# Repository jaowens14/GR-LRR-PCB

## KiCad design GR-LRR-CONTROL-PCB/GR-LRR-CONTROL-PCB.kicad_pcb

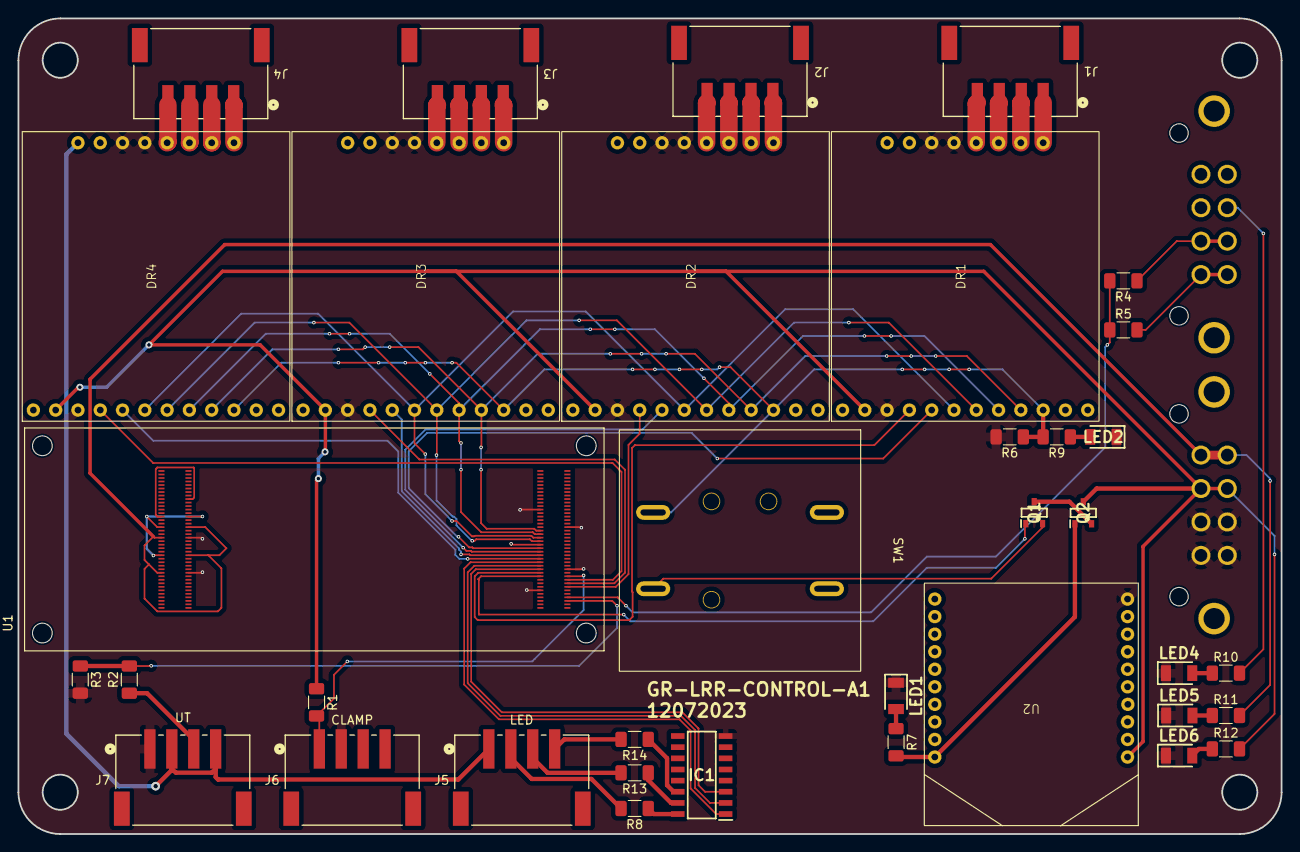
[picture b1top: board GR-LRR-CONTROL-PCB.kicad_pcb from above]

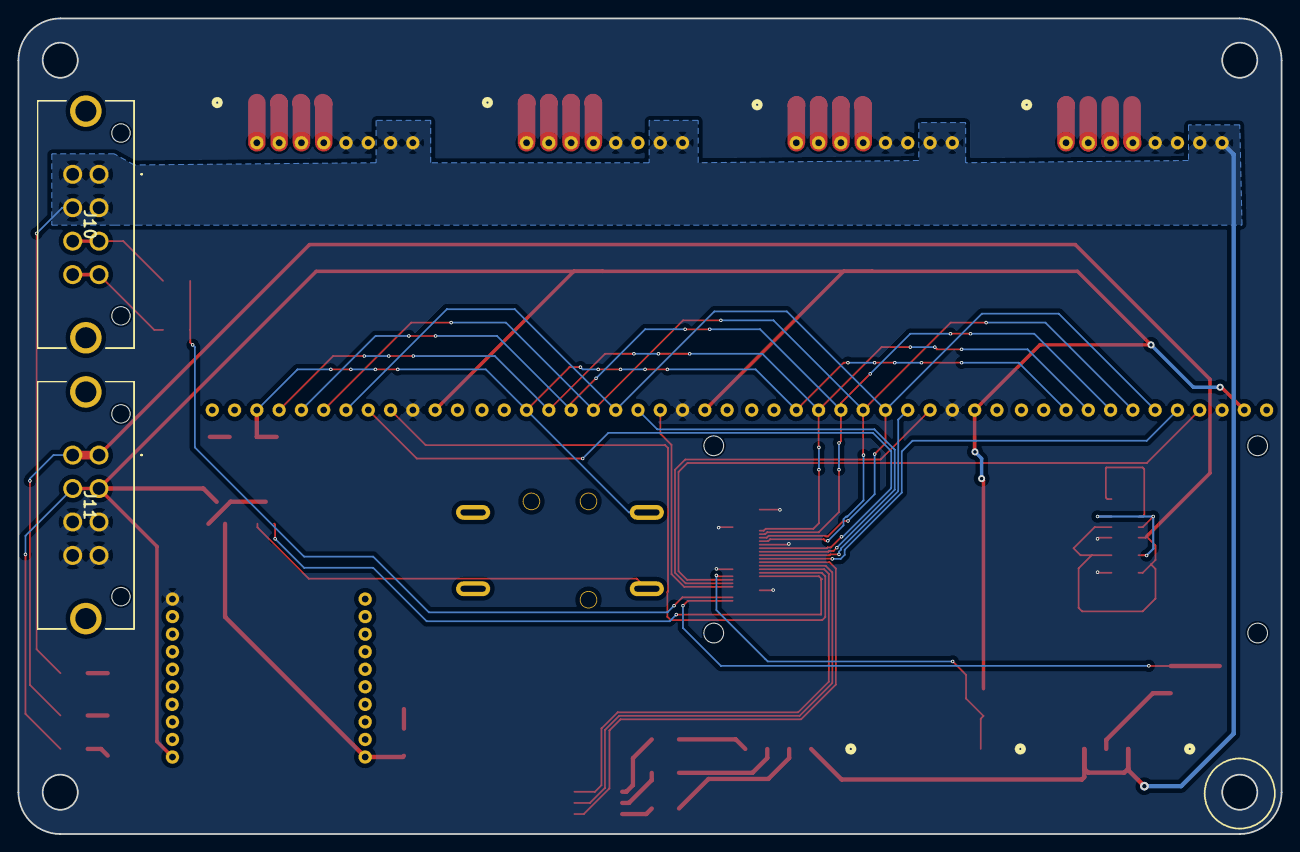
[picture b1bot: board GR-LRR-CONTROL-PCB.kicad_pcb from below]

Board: 2 copper layers, 143.9 x 92.9 mm, 38 parts (2 on the bottom side), 59 nets.

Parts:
DR1, DR2, DR3, DR4: 3730
IC1: MC1413DR2G; SOIC127P600X175-16N
J1: DRIVER 1; CONN_S4B-XH-SM4-TB_JST
J2: DRIVER 3; CONN_S4B-XH-SM4-TB_JST
J3: DRIVER 2; CONN_S4B-XH-SM4-TB_JST
J4: DRIVER 4; CONN_S4B-XH-SM4-TB_JST
J5: LED; CONN_S4B-XH-SM4-TB_JST
J6: CLAMP; CONN_S4B-XH-SM4-TB_JST
J7: UT; CONN_S4B-XH-SM4-TB_JST
J10, J11: FX30B-4S-3.81DSA; FX30B4S381DSA
LED1, LED2, LED4, LED5, LED6: QTLP650C2TR; LEDC3216X130N
Q1, Q2: BSS806NH6327XTSA1; SOT95P240X110-3N
R1, R4, R6, R8, R13, R14: 10k; R_1206_3216Metric_Pad1.30x1.75mm_HandSolder
R2: 4k; R_1206_3216Metric_Pad1.30x1.75mm_HandSolder
R3, R5: 1k; R_1206_3216Metric_Pad1.30x1.75mm_HandSolder
R7, R9, R12: 75ohm, 1/10w; R_1206_3216Metric_Pad1.30x1.75mm_HandSolder
R10: 1200ohm, 0.5w; R_1206_3216Metric_Pad1.30x1.75mm_HandSolder
R11: 180ohm, 1/10w; R_1206_3216Metric_Pad1.30x1.75mm_HandSolder
SW1: XA1E-BV302-R
U1: ABX00042; MODULE_ABX00042
U2: XB3-24AST-J

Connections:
73_ANALOG_A0: R4.2, R5.1, U1.J2_73 (ADC_A0)
75_ANALOG_A1: R2.2, R3.1, U1.J2_75 (ADC_A1)
+3.3V: DR1.2 (IOREF), DR2.2 (IOREF), DR3.2 (IOREF), DR4.2 (IOREF), J11.A2, J11.B2, Q2.3 (D), R1.1, R12.2, U2.1 (VCC)
+5V: J11.A1, J11.B1, R11.2, U1.J1_21 (VIN), U1.J1_41 (VIN)
+24V: DR1.19 (MOTOR_VIN), DR1.20 (MOTOR_VIN), DR2.19 (MOTOR_VIN), DR2.20 (MOTOR_VIN), DR3.19 (MOTOR_VIN), DR3.20 (MOTOR_VIN), DR4.19 (MOTOR_VIN), DR4.20 (MOTOR_VIN), J5.1, J7.2, J7.4, J10.A1, J10.A2, J10.B1, J10.B2, R10.2
BATT+: J10.A3, J10.B3, R4.1
BATT-: J10.A4, J10.B4, R5.2
D0 STEPPER ENABLE: Q1.1 (G), U1.J2_62 (PWM_7)
D1 STEP 1: DR1.4 (STEP/AIN1), U1.J2_60 (PWM_6)
D2 STEP 2: DR2.4 (STEP/AIN1), U1.J2_67 (PWM_5)
D3 STEP 3: DR3.4 (STEP/AIN1), U1.J2_65 (PWM_4)
D4 STEP 4: DR4.4 (STEP/AIN1), U1.J2_63 (PWM_3)
D5 CLAMP: J6.1, R1.2, U1.J2_61 (PWM_2)
D7 CS: DR1.9 (SCS), DR2.9 (SCS), DR3.9 (SCS), DR4.9 (SCS), U1.J2_36 (SPI1_CS)
D8 COPI: DR1.7 (SDATI), DR2.7 (SDATI), DR3.7 (SDATI), DR4.7 (SDATI), U1.J2_42 (SPI1_MOSI)
D9 CK: DR1.8 (SCLK), DR2.8 (SCLK), DR3.8 (SCLK), DR4.8 (SCLK), U1.J2_38 (SPI1_CK)
D10 CIPO: DR1.6 (SDATO), DR2.6 (SDATO), DR3.6 (SDATO), DR4.6 (SDATO), U1.J2_40 (SPI1_MISO)
GND: DR1.3 (GND), DR1.17 (MOTOR_GND), DR1.18 (MOTOR_GND), DR2.3 (GND), DR2.17 (MOTOR_GND), DR2.18 (MOTOR_GND), DR3.3 (GND), DR3.17 (MOTOR_GND), DR3.18 (MOTOR_GND), DR4.3 (GND), DR4.17 (MOTOR_GND), DR4.18 (MOTOR_GND), IC1.8 (GND), J6.2, J7.1, J11.A3, J11.A4, J11.B3, J11.B4, LED1.1 (K), LED2.1 (K), LED4.1 (K), LED5.1 (K), LED6.1 (K), R3.2, R6.2, U1.J1_22 (GND), U1.J1_42 (GND), U1.J2_24 (GND_1), U1.J2_33 (GND_1), U1.J2_44 (GND_1), U1.J2_57 (GND_1), U1.J2_70 (GND_1), U2.10 (GND)
GPIO0 DIR 1: DR1.5 (DIR/AIN2), U1.J2_46 (GPIO_0)
GPIO1 DIR 2: DR2.5 (DIR/AIN2), U1.J2_48 (GPIO_1)
GPIO2 DIR 3: DR3.5 (DIR/AIN2), U1.J2_50 (GPIO_2)
GPIO3 DIR 4: DR4.5 (DIR/AIN2), U1.J2_52 (GPIO_3)
GPIO4 RED LED: IC1.1 (IN_1), U1.J2_54 (GPIO_4)
GPIO5 YELLOW LED: IC1.2 (IN_2), U1.J2_56 (GPIO_5)
GPIO6 GREEN LED: IC1.3 (IN_3), U1.J2_58 (GPIO_6)
unnamed: DR1.16 (AOUT1), J1.4
unnamed: DR1.15 (AOUT2), J1.3
unnamed: DR1.14 (BOUT1), J1.2
unnamed: DR1.13 (BOUT2), J1.1
unnamed: DR2.16 (AOUT1), J2.4
unnamed: DR2.15 (AOUT2), J2.3
unnamed: DR2.14 (BOUT1), J2.2
unnamed: DR2.13 (BOUT2), J2.1
unnamed: DR3.16 (AOUT1), J3.4
unnamed: DR3.15 (AOUT2), J3.3
unnamed: DR3.14 (BOUT1), J3.2
unnamed: DR3.13 (BOUT2), J3.1
unnamed: DR4.16 (AOUT1), J4.4
unnamed: DR4.15 (AOUT2), J4.3
unnamed: DR4.14 (BOUT1), J4.2
unnamed: DR4.13 (BOUT2), J4.1
unnamed: IC1.14 (OUT_5), R14.1
unnamed: IC1.15 (OUT_6), R13.1
unnamed: IC1.16 (OUT_7), R8.1
unnamed: J5.2, R8.2
unnamed: J5.3, R13.2
unnamed: J5.4, R14.2
unnamed: J7.3, R2.1
unnamed: LED1.2 (A), R7.1
unnamed: LED2.2 (A), R9.1
unnamed: LED4.2 (A), R10.1
unnamed: LED5.2 (A), R11.1
unnamed: LED6.2 (A), R12.1
unnamed: Q1.3 (D), Q2.2 (S)
unnamed: Q1.2 (S), SW1.3
unnamed: U1.J1_31 (GND), U1.J1_47 (GND), U1.J1_54 (GND)
unnamed: U1.J1_53 (VSYS), U1.J1_64 (VSYS)
STEPPER_ENABLE: DR1.10 (!SLEEP), DR2.10 (!SLEEP), DR3.10 (!SLEEP), DR4.10 (!SLEEP), R6.1, R9.2, SW1.4
ZIGBEE_IO: Q2.1 (G), R7.2, U2.20 (AD0/DIO0)

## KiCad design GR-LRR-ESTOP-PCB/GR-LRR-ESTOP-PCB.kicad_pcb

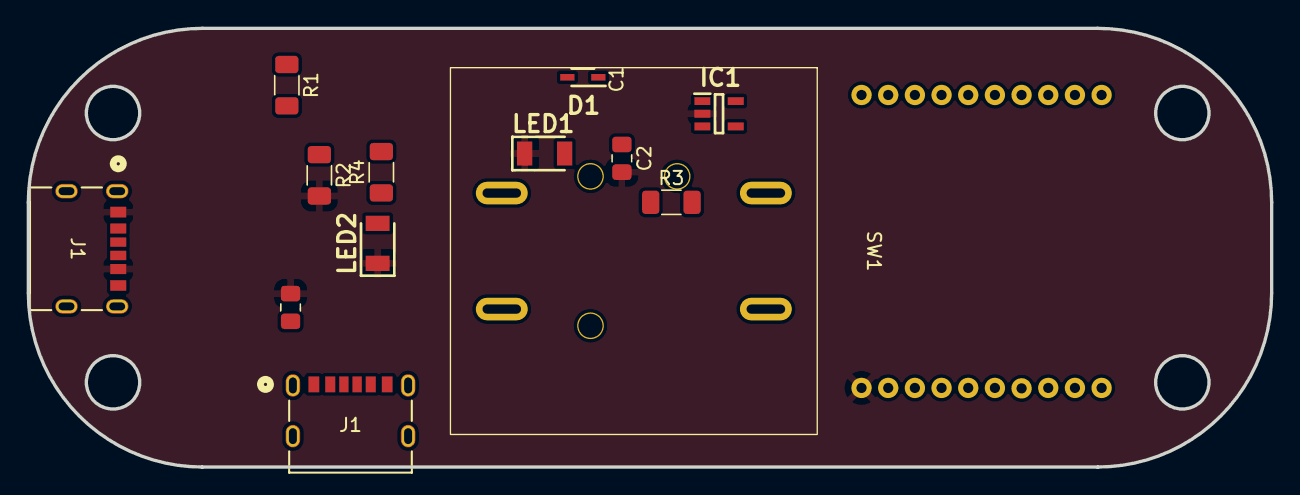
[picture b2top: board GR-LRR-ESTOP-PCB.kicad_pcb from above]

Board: 2 copper layers, 93.2 x 32.9 mm, 14 parts (1 on the bottom side), 8 nets, no tracks yet.

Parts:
C1, C2: 1uF, 10V; C_0805_2012Metric_Pad1.18x1.45mm_HandSolder
D1: ZLLS400TA; SOD2513X120N
IC1: TLV75533PDBVR; SOT95P280X145-5N
J1, J1#2: 10164359-00011LF; CONN_10164359-00011LF_AMP
LED1, LED2: QTLP650C2TR; LEDC3216X130N
R1, R2: 1k; R_1206_3216Metric_Pad1.30x1.75mm_HandSolder
R3, R4: 86ohm, 1/10w; R_1206_3216Metric_Pad1.30x1.75mm_HandSolder
SW1: XA1E-BV302-R
U1: XB3-24AST-J

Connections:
+3.3V: C2.1, IC1.5 (OUT), R3.2, SW1.1, U1.1 (VCC)
+5V: D1.2 (A), J1#2.A12 (VBUS), J1#2.B5 (VBUS)
GND: C1.2, C2.2, IC1.2 (GND), J1#2.A9 (GND), J1#2.B12 (GND), LED1.1 (K), LED2.1 (K), R2.2, U1.10 (GND)
unnamed: C1.1, D1.1 (K), IC1.1 (IN), IC1.3 (EN)
unnamed: LED1.2 (A), R3.1
unnamed: LED2.2 (A), R4.1
unnamed: R1.1, SW1.2
unnamed: R1.2, R2.1, R4.2, U1.20 (AD0/DIO0)

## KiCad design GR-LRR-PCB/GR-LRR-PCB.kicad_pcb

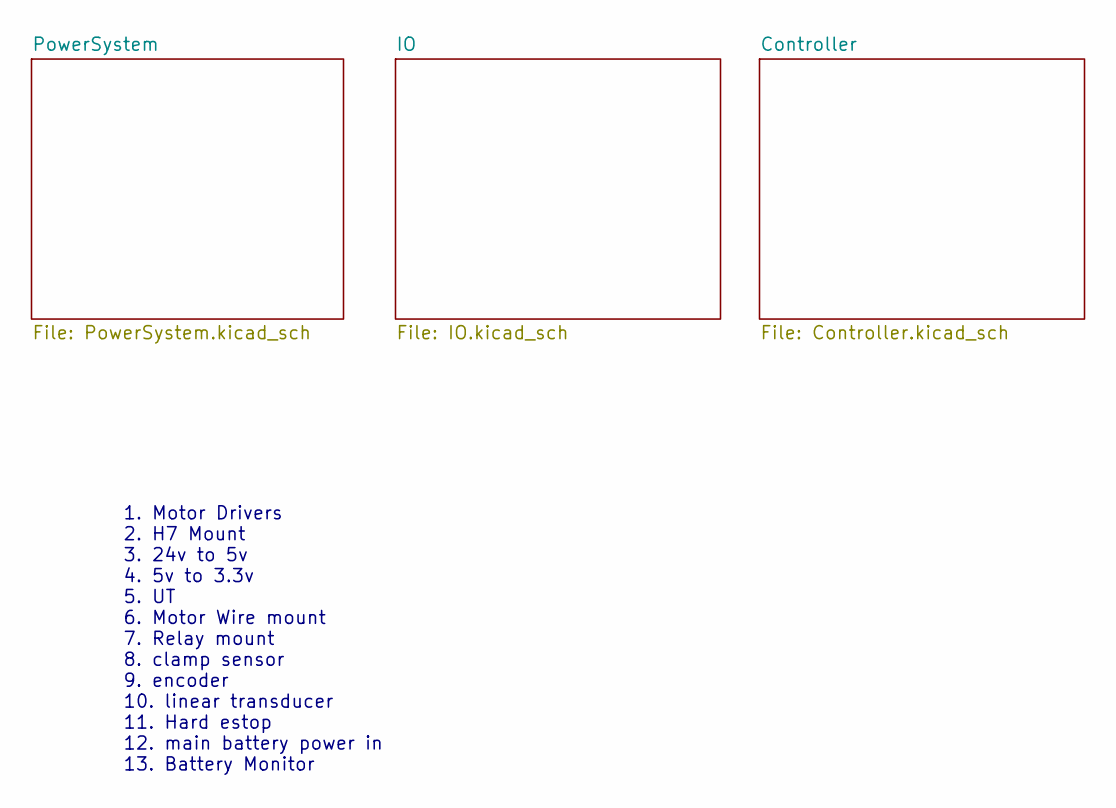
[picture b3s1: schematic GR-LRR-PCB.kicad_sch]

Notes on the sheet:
1. Motor Drivers 2. H7 Mount 3. 24v to 5v 4. 5v to 3.3v 5. UT 6. Motor Wire mount 7. Relay mount 8. clamp sensor 9. encoder 10. linear transducer 11. Hard estop 12. main battery power in 13. Battery Monitor

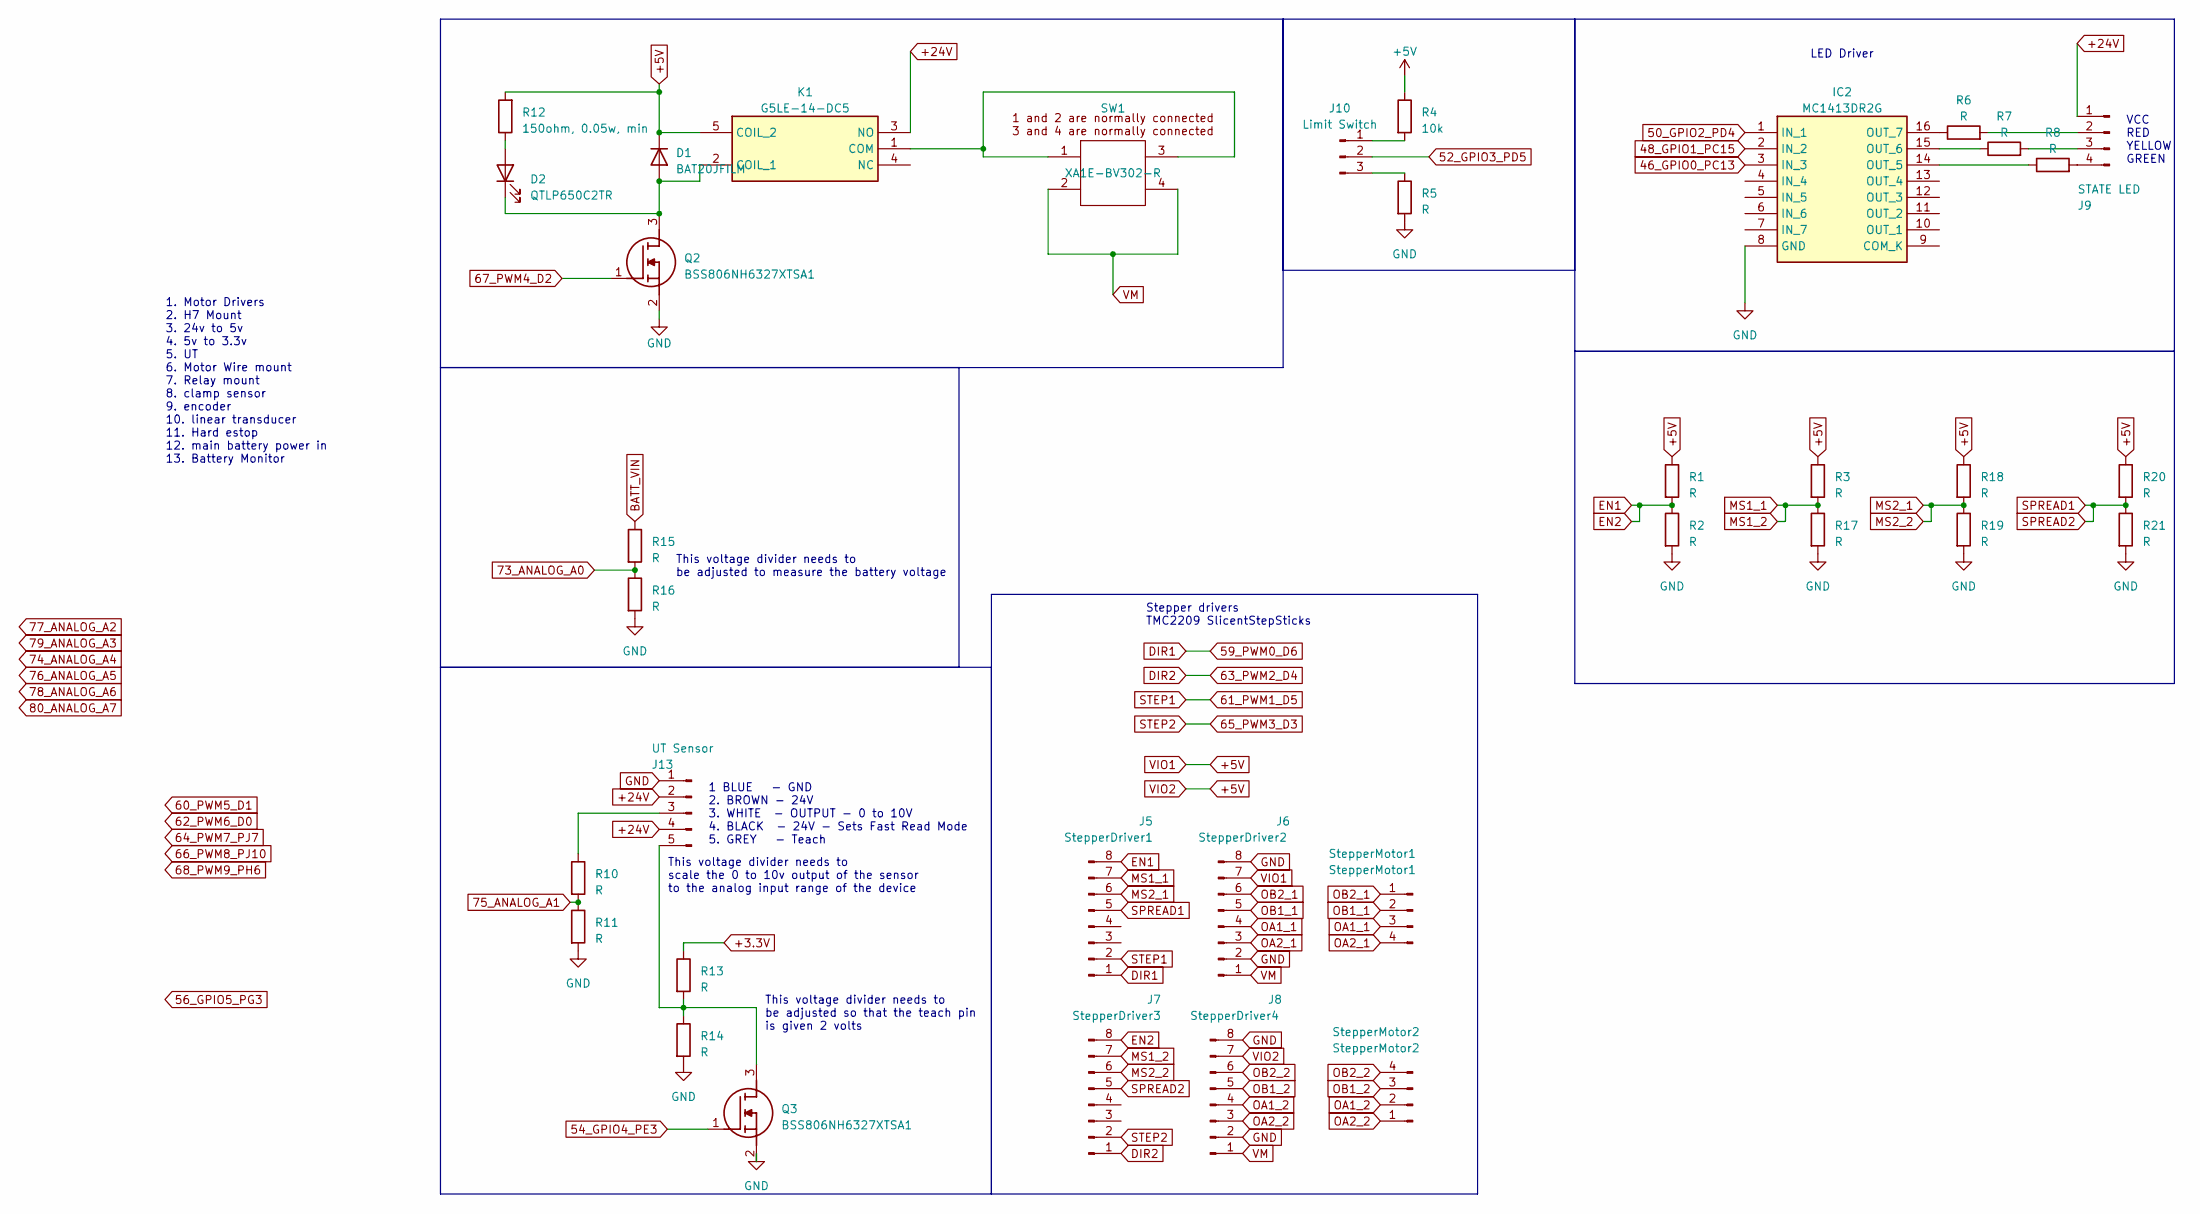
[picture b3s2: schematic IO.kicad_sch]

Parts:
D1: BAT20JFILM; D_SOD-323_HandSoldering
D2: QTLP650C2TR; D_1206_3216Metric_Pad1.42x1.75mm_HandSolder
IC2: MC1413DR2G; SOIC127P600X175-16N; Mouser Part Number 863-MC1413DR2G
J5: StepperDriver1; PinHeader_1x08_P2.54mm_Vertical
J6: StepperDriver2; PinHeader_1x08_P2.54mm_Vertical
J7: StepperDriver3; PinHeader_1x08_P2.54mm_Vertical
J8: StepperDriver4; PinHeader_1x08_P2.54mm_Vertical
J9: STATE LED; PinHeader_1x04_P2.54mm_Vertical; Part Number JR28-RYG-D
J10: Limit Switch; PinHeader_1x03_P2.54mm_Vertical
J13: UT Sensor; PinHeader_1x05_P2.54mm_Vertical
K1: G5LE-14-DC5; G5LE-14_SPDT; Mouser Part Number 653-G5LE-14-DC5
Q2, Q3: BSS806NH6327XTSA1; SOT95P240X110-3N; Mouser Part Number 726-BSS806NH6327
R1, R2, R3, R5, R6, R7, R8, R10, R11, R13, R14, R15, R16, R17, R18, R19, R20, R21: R; R_1206_3216Metric_Pad1.30x1.75mm_HandSolder
R4: 10k; R_1206_3216Metric_Pad1.30x1.75mm_HandSolder
R12: 150ohm, 0.05w, min; R_1206_3216Metric_Pad1.30x1.75mm_HandSolder; Part Number RMCF1206JT300R
SW1: XA1E-BV302-R
StepperMotor1: StepperMotor1; PinHeader_1x04_P2.54mm_Vertical
StepperMotor2: StepperMotor2; PinHeader_1x04_P2.54mm_Vertical

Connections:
46_GPIO0_PC13: IC2.3 (IN_3); also elsewhere on the board
48_GPIO1_PC15: IC2.2 (IN_2); also elsewhere on the board
50_GPIO2_PD4: IC2.1 (IN_1); also elsewhere on the board
52_GPIO3_PD5: J10.2; also elsewhere on the board
54_GPIO4_PE3: Q3.1 (G); also elsewhere on the board
59_PWM0_D6: J5.1; also elsewhere on the board
61_PWM1_D5: J5.2; also elsewhere on the board
63_PWM2_D4: J7.1; also elsewhere on the board
65_PWM3_D3: J7.2; also elsewhere on the board
67_PWM4_D2: Q2.1 (G); also elsewhere on the board
73_ANALOG_A0: R15.2, R16.1; also elsewhere on the board
75_ANALOG_A1: R10.2, R11.1; also elsewhere on the board
+3.3V: R13.1; also elsewhere on the board
+5V: D1.1 (K), J6.7, J8.7, K1.5 (COIL_2), R1.1, R3.1, R4.1, R12.2, R18.1, R20.1; also elsewhere on the board
+24V: J9.1, J13.2, J13.4, K1.3 (NO); also elsewhere on the board
BATT_VIN: R15.1; also elsewhere on the board
EN1: J5.8, J7.8, R1.2, R2.1
GND: IC2.8 (GND), J6.2, J6.8, J8.2, J8.8, J13.1, Q2.2 (S), Q3.2 (S), R2.2, R5.2, R11.2, R14.2, R16.2, R17.2, R19.2, R21.2; also elsewhere on the board
MS1_1: J5.7, J7.7, R3.2, R17.1
MS2_1: J5.6, J7.6, R18.2, R19.1
unnamed: D1.2 (A), D2.1 (K), K1.2 (COIL_1), Q2.3 (D)
unnamed: D2.2 (A), R12.1
unnamed: IC2.14 (OUT_5), R8.1
unnamed: IC2.15 (OUT_6), R7.1
unnamed: IC2.16 (OUT_7), R6.1
unnamed: J9.2, R6.2
unnamed: J9.3, R7.2
unnamed: J9.4, R8.2
unnamed: J10.1, R4.2
unnamed: J10.3, R5.1
unnamed: J13.3, R10.1
unnamed: J13.5, Q3.3 (D), R13.2, R14.1
unnamed: K1.1 (COM), SW1.1, SW1.3
OA1_1: J6.4, StepperMotor1.3
OA1_2: J8.4, StepperMotor2.2
OA2_1: J6.3, StepperMotor1.4
OA2_2: J8.3, StepperMotor2.1
OB1_1: J6.5, StepperMotor1.2
OB1_2: J8.5, StepperMotor2.3
OB2_1: J6.6, StepperMotor1.1
OB2_2: J8.6, StepperMotor2.4
SPREAD1: J5.5, J7.5, R20.2, R21.1
VM: J6.1, J8.1, SW1.2, SW1.4

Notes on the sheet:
This voltage divider needs to be adjusted to measure the battery voltage
LED Driver
VCC RED YELLOW GREEN
1. Motor Drivers 2. H7 Mount 3. 24v to 5v 4. 5v to 3.3v 5. UT 6. Motor Wire mount 7. Relay mount 8. clamp sensor 9. encoder 10. linear transducer 11. Hard estop 12. main battery power in 13. Battery Monitor
1 BLUE - GND 2. BROWN - 24V 3. WHITE - OUTPUT - 0 to 10V 4. BLACK - 24V - Sets Fast Read Mode 5. GREY - Teach
This voltage divider needs to be adjusted so that the teach pin is given 2 volts
Stepper drivers TMC2209 SlicentStepSticks
This voltage divider needs to scale the 0 to 10v output of the sensor to the analog input range of the device

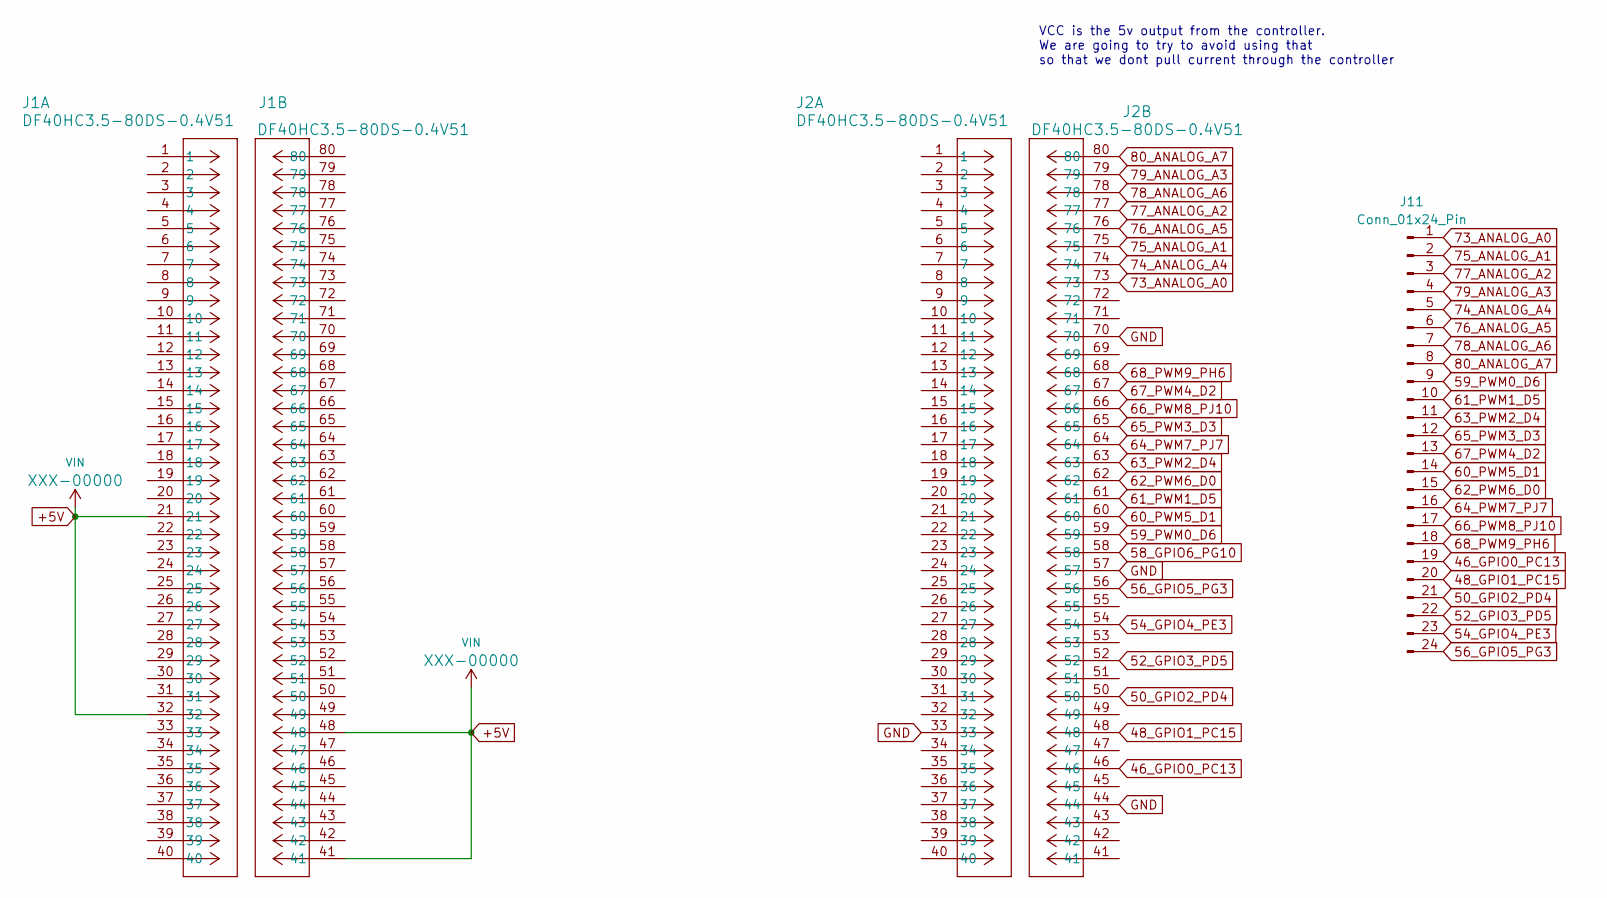
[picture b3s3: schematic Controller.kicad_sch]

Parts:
J1, J2: DF40HC3.5-80DS-0.4V51; DF40HC3580DS04V58
J11: Conn_01x24_Pin; PinHeader_1x24_P2.54mm_Vertical

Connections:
46_GPIO0_PC13: J2.46, J11.19; also elsewhere on the board
48_GPIO1_PC15: J2.48, J11.20; also elsewhere on the board
50_GPIO2_PD4: J2.50, J11.21; also elsewhere on the board
52_GPIO3_PD5: J2.52, J11.22; also elsewhere on the board
54_GPIO4_PE3: J2.54, J11.23; also elsewhere on the board
56_GPIO5_PG3: J2.56, J11.24
58_GPIO6_PG10: J2.58
59_PWM0_D6: J2.59, J11.9; also elsewhere on the board
60_PWM5_D1: J2.60, J11.14
61_PWM1_D5: J2.61, J11.10; also elsewhere on the board
62_PWM6_D0: J2.62, J11.15
63_PWM2_D4: J2.63, J11.11; also elsewhere on the board
64_PWM7_PJ7: J2.64, J11.16
65_PWM3_D3: J2.65, J11.12; also elsewhere on the board
66_PWM8_PJ10: J2.66, J11.17
67_PWM4_D2: J2.67, J11.13; also elsewhere on the board
68_PWM9_PH6: J2.68, J11.18
73_ANALOG_A0: J2.73, J11.1; also elsewhere on the board
74_ANALOG_A4: J2.74, J11.5
75_ANALOG_A1: J2.75, J11.2; also elsewhere on the board
76_ANALOG_A5: J2.76, J11.6
77_ANALOG_A2: J2.77, J11.3
78_ANALOG_A6: J2.78, J11.7
79_ANALOG_A3: J2.79, J11.4
80_ANALOG_A7: J2.80, J11.8
+5V: J1.21, J1.32, J1.41, J1.48; also elsewhere on the board
GND: J2.33, J2.44, J2.57, J2.70; also elsewhere on the board

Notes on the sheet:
VCC is the 5v output from the controller. We are going to try to avoid using that so that we dont pull current through the controller

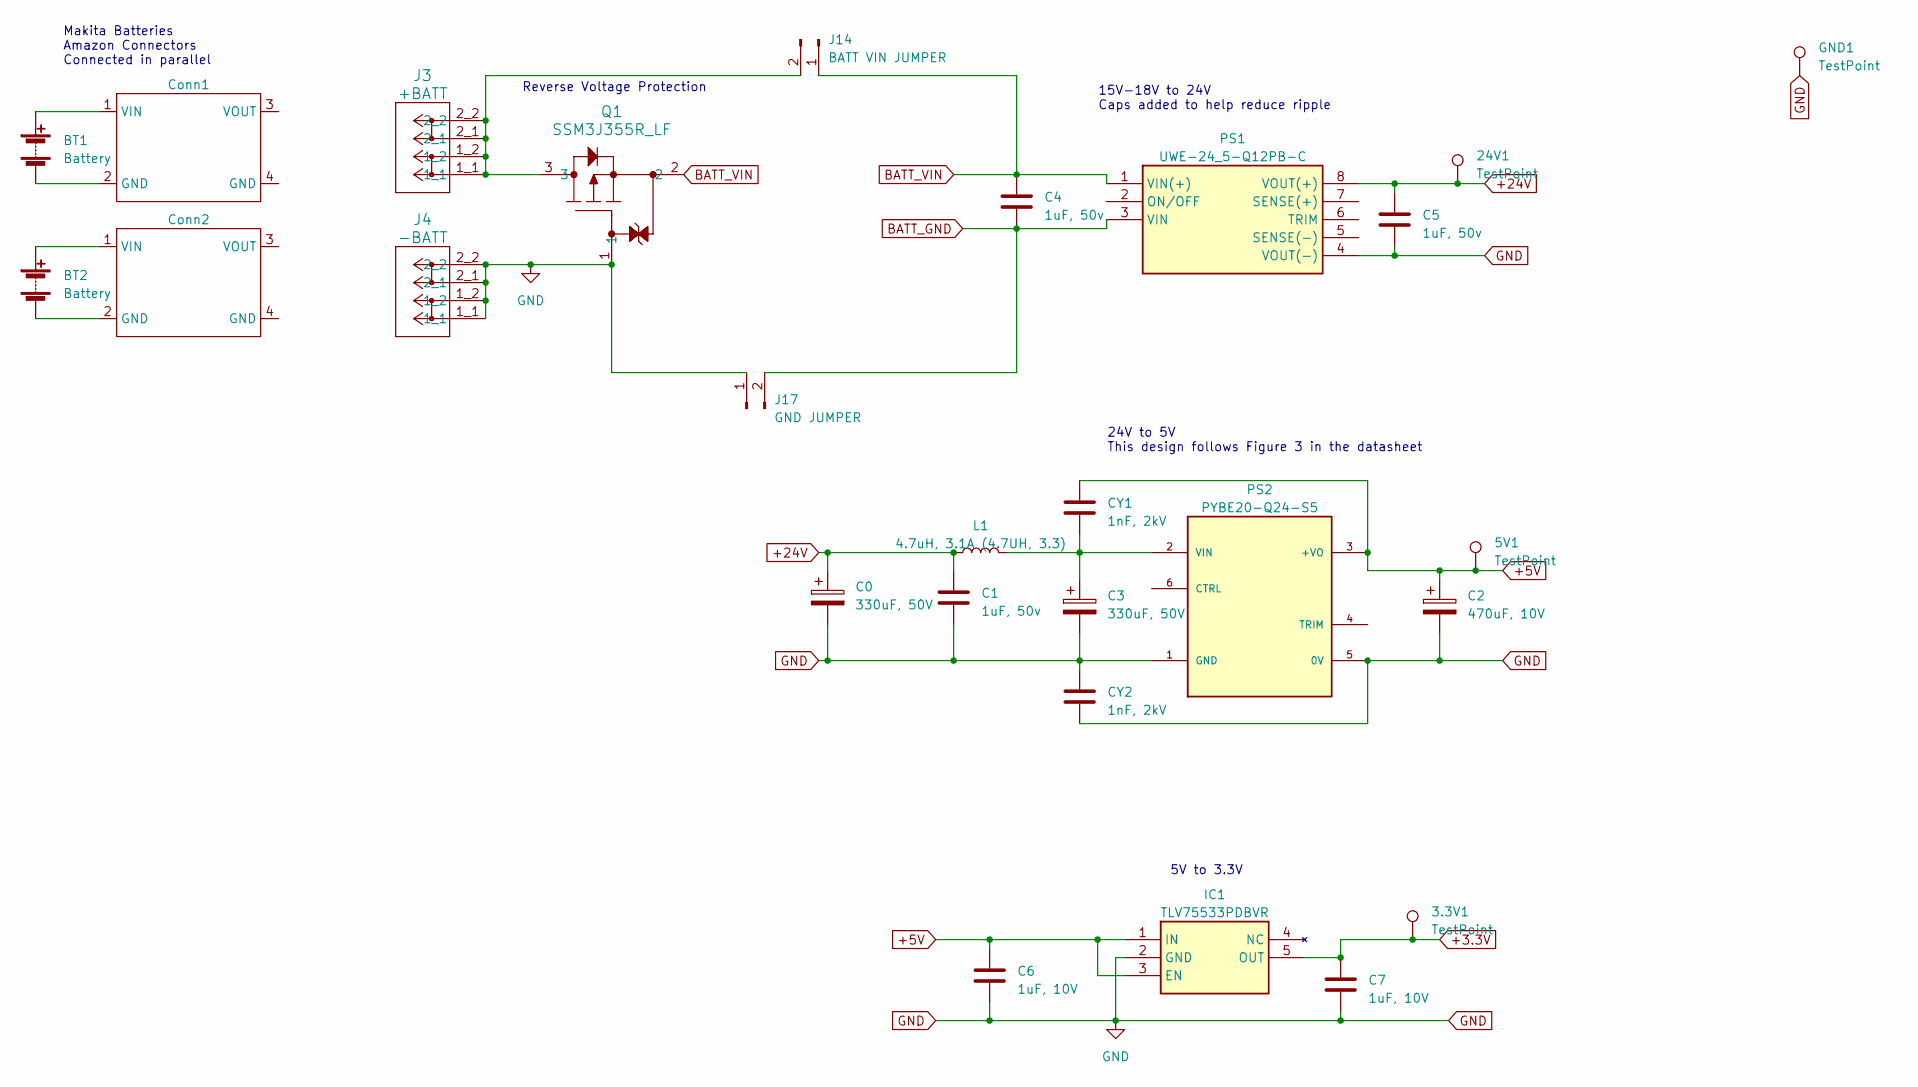
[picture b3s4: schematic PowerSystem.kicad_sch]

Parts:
3.3V1, 5V1, 24V1: TestPoint; TestPoint_Pad_D2.5mm
BT1, BT2: Battery
C0, C3: 330uF, 50V; CP_Radial_D10.0mm_P5.00mm; Part Number ECA-1HM331B
C1, C4, C5: 1uF, 50v; C_0805_2012Metric_Pad1.18x1.45mm_HandSolder; Part Number CL21B105KBFNNNG
C2: 470uF, 10V; CP_EIA-7343-15_Kemet-W_Pad2.25x2.55mm_HandSolder; Part Number 293D477X9010E2TE3
C6, C7: 1uF, 10V; C_0805_2012Metric_Pad1.18x1.45mm_HandSolder; Part Number CL21B105KPFNNNE
CY1, CY2: 1nF, 2kV; C_1812_4532Metric_Pad1.57x3.40mm_HandSolder; Part Number C1812C102KGRACAUTO
Conn1, Conn2: (no value)
GND1: TestPoint; TestPoint_Pad_D2.5mm
IC1: TLV75533PDBVR; SOT95P280X145-5N; Mouser Part Number 595-TLV75533PDBVR
J3: +BATT; 2604-1102
J4: -BATT; 2604-1102
J14: BATT VIN JUMPER; PinHeader_1x02_P2.54mm_Vertical
J17: GND JUMPER; PinHeader_1x02_P2.54mm_Vertical
L1: 4.7uH, 3.1A (4.7UH, 3.3); IND_XGL4018_COC-M; Part Number XGL4018-472MEC
PS1: UWE-24_5-Q12PB-C; UWE245Q12PBC; Mouser Part Number 580-UWE-24/5-Q12PB-C
PS2: PYBE20-Q24-S5; CONV_PYBE20-Q24-S5
Q1: SSM3J355R_LF; SOT-23F_TOS

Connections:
+3.3V: 3.3V1.1, C7.1, IC1.5 (OUT); also elsewhere on the board
+5V: 5V1.1, C2.1, C6.1, CY1.1, IC1.1 (IN), IC1.3 (EN), PS2.3 (+VO); also elsewhere on the board
+24V: 24V1.1, C0.1, C1.1, C5.1, L1.1, PS1.8 (VOUT(+)); also elsewhere on the board
BATT_GND: C4.2, J17.2, PS1.3 (VIN)
BATT_VIN: C4.1, J14.1, PS1.1 (VIN(+)), Q1.2; also elsewhere on the board
GND: C0.2, C1.2, C2.2, C3.2, C5.2, C6.2, C7.2, CY2.1, CY2.2, GND1.1, IC1.2 (GND), J4.1_1, J4.1_2, J4.2_1, J4.2_2, J17.1, PS1.4 (VOUT(-)), PS2.1 (GND), PS2.5 (0V), Q1.1; also elsewhere on the board
unnamed: BT1.1 (+), Conn1.1 (VIN)
unnamed: BT1.2 (-), Conn1.2 (GND)
unnamed: BT2.1 (+), Conn2.1 (VIN)
unnamed: BT2.2 (-), Conn2.2 (GND)
unnamed: J3.1_1, J3.1_2, J3.2_1, J3.2_2, J14.2, Q1.3
unnamed: C3.1, CY1.2, L1.2, PS2.2 (VIN)

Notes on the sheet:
Makita Batteries Amazon Connectors Connected in parallel
5V to 3.3V
15V-18V to 24V Caps added to help reduce ripple
Reverse Voltage Protection
24V to 5V This design follows Figure 3 in the datasheet

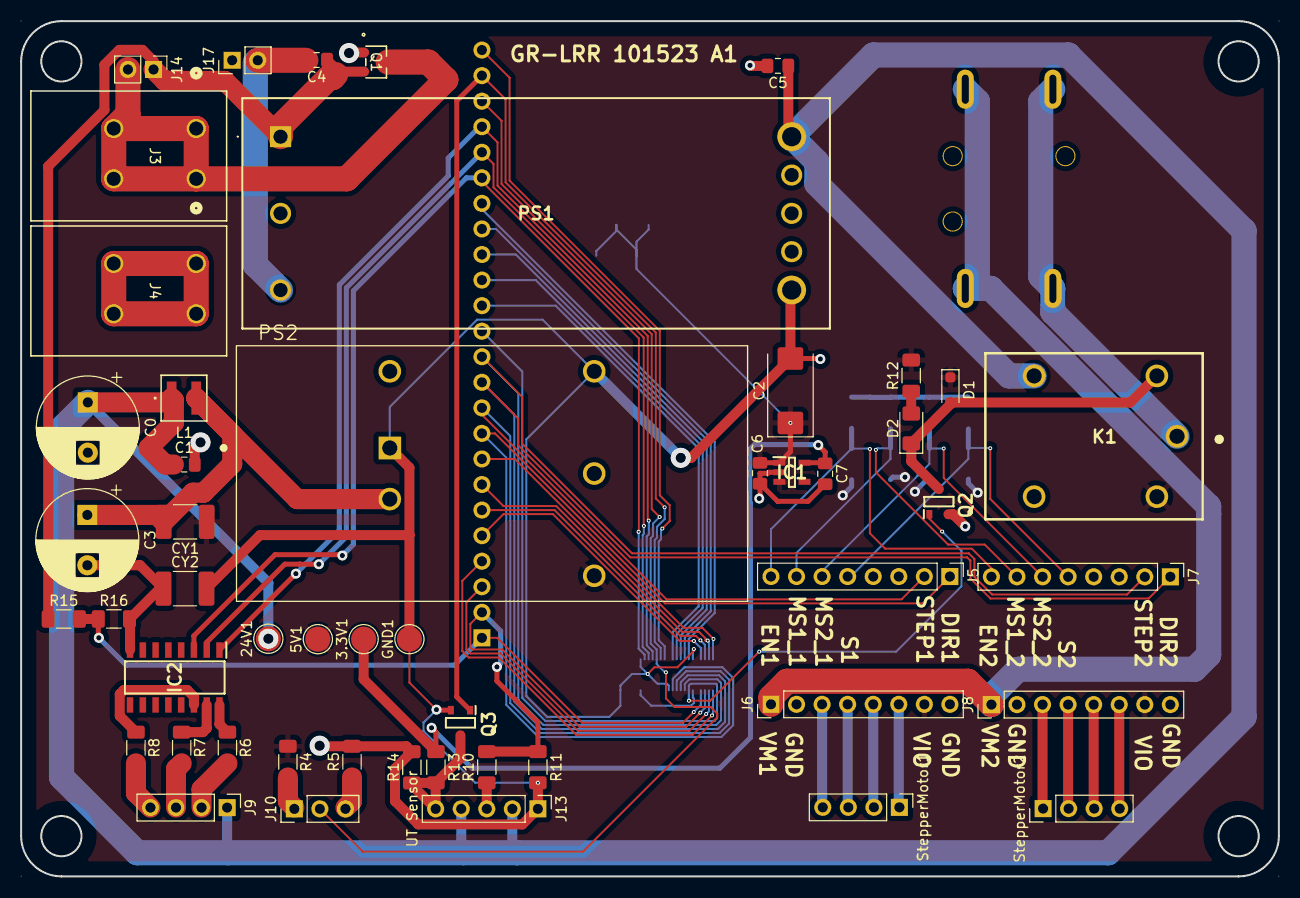
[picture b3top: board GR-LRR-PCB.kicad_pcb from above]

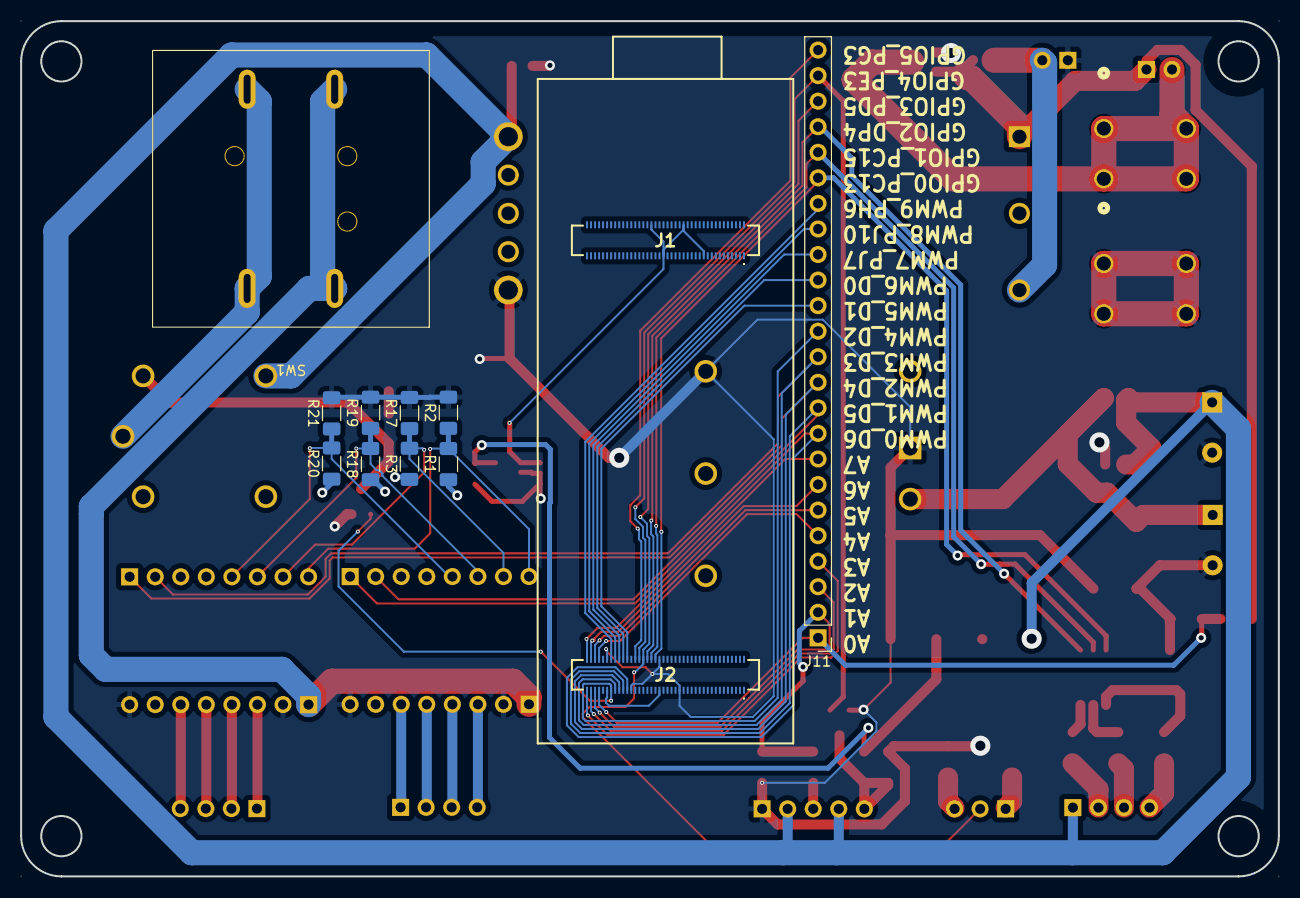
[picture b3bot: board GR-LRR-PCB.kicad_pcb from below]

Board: 2 copper layers, 125.0 x 85.0 mm, 62 parts (12 on the bottom side), 58 nets.

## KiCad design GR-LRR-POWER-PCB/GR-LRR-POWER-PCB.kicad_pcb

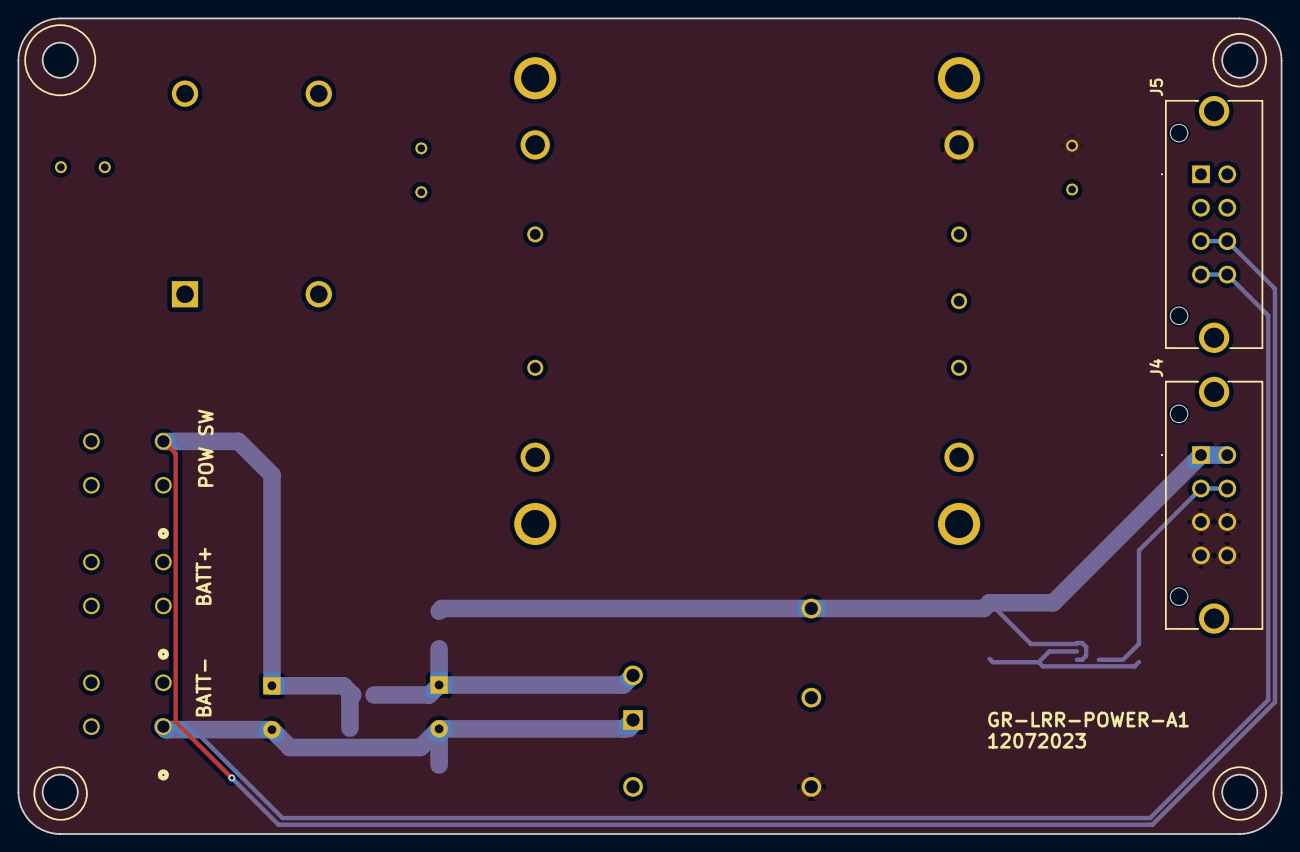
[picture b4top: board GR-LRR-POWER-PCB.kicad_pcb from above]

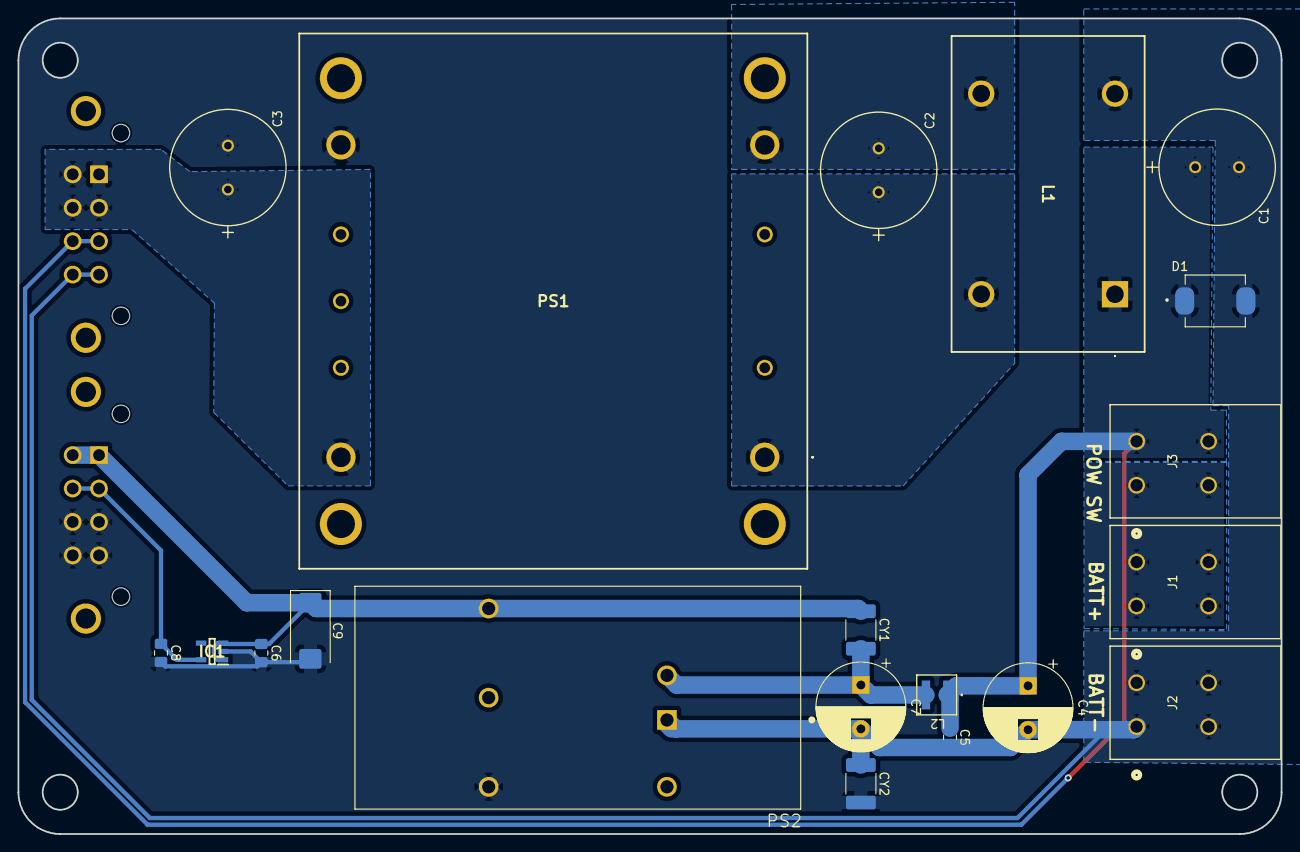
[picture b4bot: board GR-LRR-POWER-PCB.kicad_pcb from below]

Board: 2 copper layers, 143.9 x 92.9 mm, 22 parts (20 on the bottom side), 10 nets.

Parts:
C1, C2, C3: 100PX220MEFC12.5X20; CAP_PK&slash_PZ_12P5X20_LOW_RUB
C4, C7: 330uF, 50V; CP_Radial_D10.0mm_P5.00mm
C5: 1uF, 50v; C_0805_2012Metric_Pad1.18x1.45mm_HandSolder
C6, C8: 1uF, 10V; C_0805_2012Metric_Pad1.18x1.45mm_HandSolder
C9: 470uF, 10V; CP_EIA-7343-15_Kemet-W_Pad2.25x2.55mm_HandSolder
CY1, CY2: 1nF, 2kV; C_1812_4532Metric_Pad1.57x3.40mm_HandSolder
D1: SMCJ40A; DIOM7959X262N
IC1: TLV75533PDBVR; SOT95P280X145-5N
J1: BATT1; 2604-1102
J2: BATT2; 2604-1102
J3: POW_SW; 2604-1102
J4, J5: FX30B-4P-3.81DSA25; FX30B4P381DSA25
L1: 047700
L2: 4.7uH, 3.1A (4.7UH, 3.3); IND_XGL4018_COC-M
PS1: QSB30024S24
PS2: PYBE20-Q24-S5; CONV_PYBE20-Q24-S5

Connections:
+3.3V: C8.1, IC1.5 (OUT), J4.B1, J4.B2
+5V: C6.1, C9.1, CY1.1, IC1.1 (IN), IC1.3 (EN), J4.A1, J4.A2, PS2.3 (+VO)
+24V: C3.1, J5.A1, J5.A2, J5.B1, J5.B2, PS1.9 (+VOUT)
BATT+: C1.1, C4.1, C5.1, D1.C, J3.2_1, J3.2_2, J5.C1, J5.C2, L1.1, L2.1
BATT-: C1.2, C4.2, C5.2, C7.2, CY2.1, D1.A, J2.1_1, J2.1_2, J2.2_1, J2.2_2, J5.D1, J5.D2, L1.2, PS2.1 (GND)
GND: C3.2, C6.2, C8.2, C9.2, CY2.2, IC1.2 (GND), J4.C1, J4.C2, J4.D1, J4.D2, PS1.5 (-VOUT), PS2.5 (0V)
unnamed: J1.1_1, J1.1_2, J1.2_1, J1.2_2, J3.1_1, J3.1_2
unnamed: C2.1, L1.4, PS1.1 (+VIN)
unnamed: C2.2, L1.3, PS1.4 (-VIN)
unnamed: C7.1, CY1.2, L2.2, PS2.2 (VIN)
